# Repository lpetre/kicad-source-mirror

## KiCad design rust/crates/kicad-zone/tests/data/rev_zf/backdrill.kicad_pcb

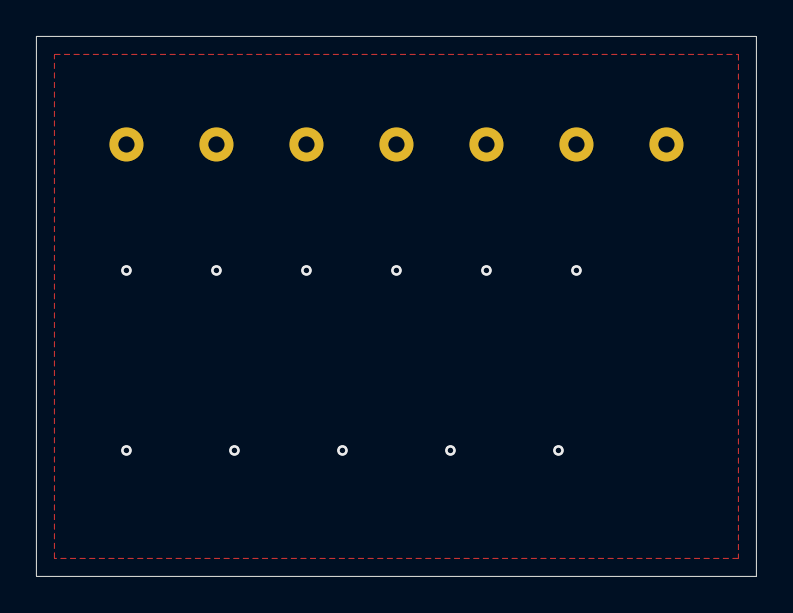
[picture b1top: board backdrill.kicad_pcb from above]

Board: 4 copper layers, 40.0 x 30.0 mm, 7 parts (0 on the bottom side), 2 nets, no tracks yet.

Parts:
J1: V; J1
J2: V; J2
J3: V; J3
J4: V; J4
J5: V; J5
J6: V; J6
J7: V; J7

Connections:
A: J1.1, J3.3, J4.4, J6.6, J7.7
B: J2.2, J5.5

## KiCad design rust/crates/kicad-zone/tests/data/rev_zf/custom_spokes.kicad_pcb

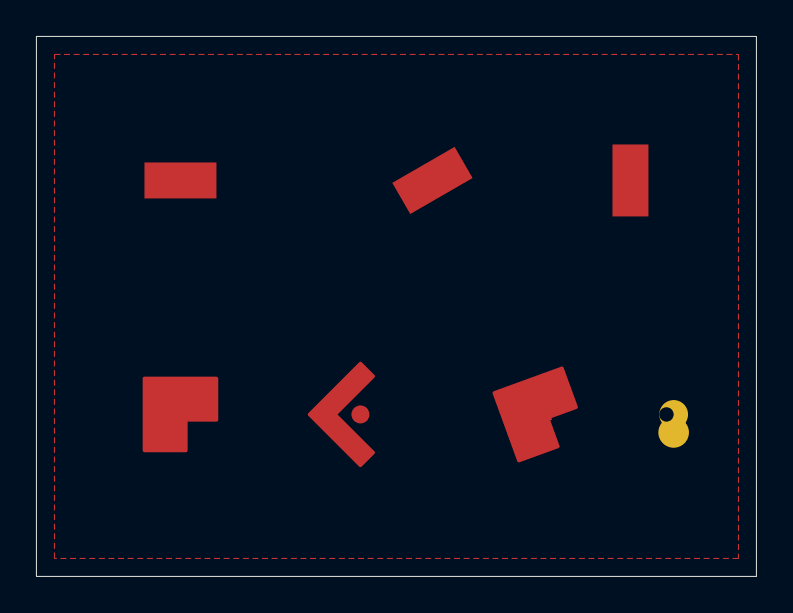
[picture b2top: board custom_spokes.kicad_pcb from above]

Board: 2 copper layers, 40.0 x 30.0 mm, 7 parts (0 on the bottom side), 2 nets, no tracks yet.

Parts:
U1: V; U1
U2: V; U2
U3: V; U3
U4: V; U4
U5: V; U5
U6: V; U6
U7: V; U7

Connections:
A: U1.1, U2.1, U3.1, U6.1, U7.1
B: U4.1, U5.1

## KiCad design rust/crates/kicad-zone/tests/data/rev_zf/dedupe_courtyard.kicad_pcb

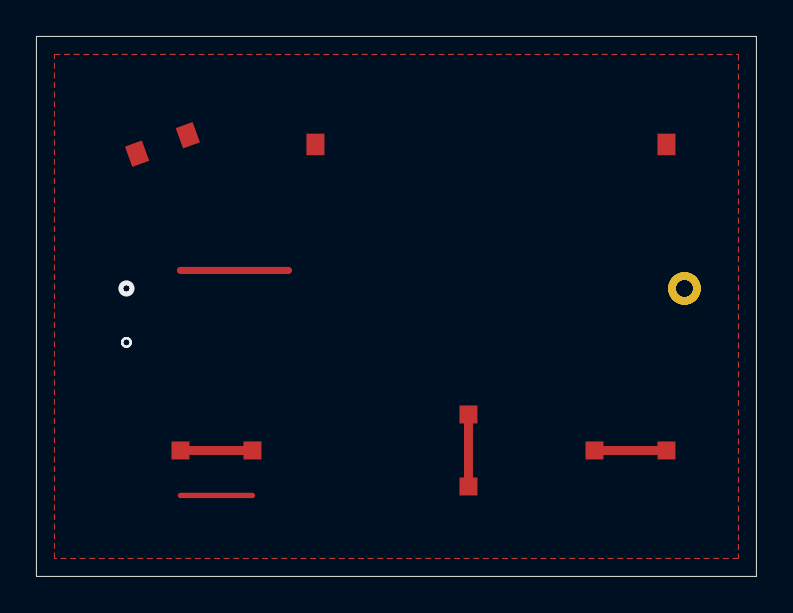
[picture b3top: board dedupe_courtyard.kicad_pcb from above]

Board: 4 copper layers, 40.0 x 30.0 mm, 10 parts (1 on the bottom side), 2 nets.

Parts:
C1: V; C1
C2: V; C2
C3: V; C3
C4: V; C4
D1: V; D1
D2: V; D2
D3: V; D3
NT1: V; NT1
NT2: V; NT2
NT3: V; NT3

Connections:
A: C1.2, D3.1, NT1.1, NT3.1
B: C1.1, C2.1, C3.1, C4.1, D1.1, D2.1, NT1.2, NT2.1, NT3.2
